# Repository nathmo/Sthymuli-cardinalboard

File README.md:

# Sthymuli-cardinalboard
companion boardto the sthymuli motherboard

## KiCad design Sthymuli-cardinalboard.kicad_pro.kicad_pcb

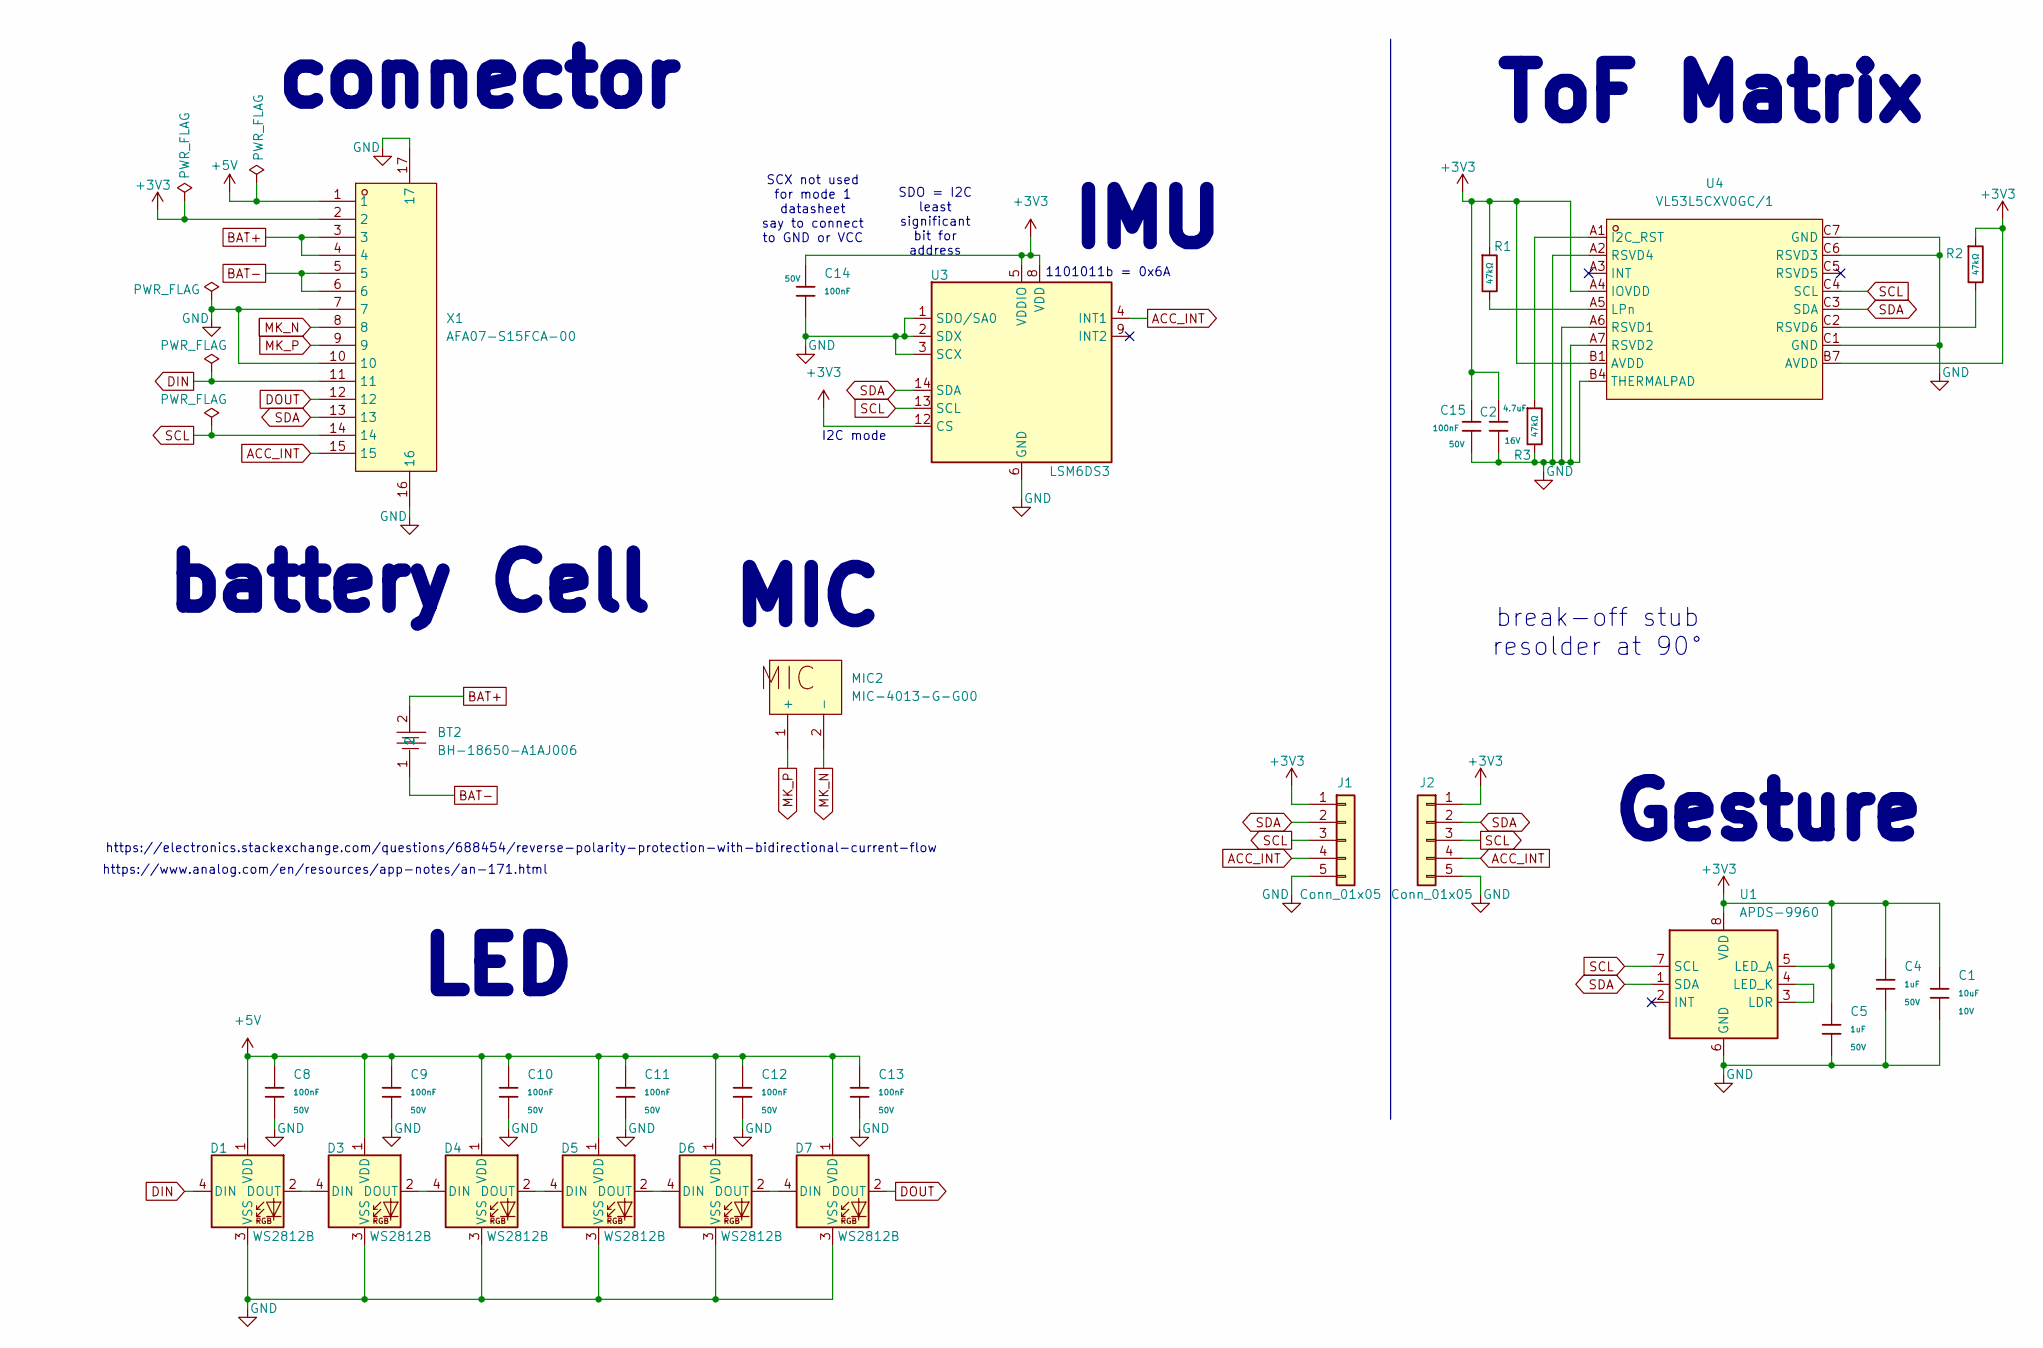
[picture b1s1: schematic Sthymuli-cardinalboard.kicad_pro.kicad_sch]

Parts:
BT2: BH-18650-A1AJ006; BAT-TH_BH-18650-A1AJ006; MPN BH-18650-A1AJ006; LCSC Part C5290175
C1: 10uF; C_0603; Voltage Rated 10V; Tolerance ±10%; Part CL10A106KP8NNNC; LCSC C19702
C2: 4.7uF; C_0603; Voltage Rated 16V; Tolerance ±10%; Part CL10A475KO8NNNC; LCSC C19666
C4, C5: 1uF; C_0603; Voltage Rated 50V; Tolerance ±10%; Part CL10A105KB8NNNC; LCSC C15849
C8, C9, C10, C11, C12, C13, C14, C15: 100nF; C_0603; Voltage Rated 50V; Tolerance ±10%; Part CC0603KRX7R9BB104; LCSC C14663
D1, D3, D4, D5, D6, D7: WS2812B; LED_WS2812B_PLCC4_5.0x5.0mm_P3.2mm
J1: Conn_01x05; PinHeader_1x05_P2.54mm_Vertical_SMD_Pin1Left
J2: Conn_01x05; PinHeader_1x05_P2.54mm_Horizontal
MIC2: MIC-4013-G-G00; MIC-SMD_BD4.0-4013_SMDA; MPN MIC-4013-G-G00; LCSC Part C42371093
R1, R2, R3: 47kΩ; R_0603; Overload Voltage (Max) 75V; Tolerance ±1%; Part 0603WAF4702T5E; LCSC C25819
U1: APDS-9960; Avago_APDS-9960
U3: LSM6DS3; LGA-14_3x2.5mm_P0.5mm_LayoutBorder3x4y
U4: VL53L5CXV0GC/1; LGA-16_L6.4-W3.0_VL53L5CXV0GC-1; MPN VL53L5CXV0GC/1; LCSC Part C3178303
X1: AFA07-S15FCA-00; FPC-SMD_15P-P1.00_JS_AFA07-S15XXX; MPN AFA07-S15FCA-00; LCSC Part C262721

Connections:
+3V3: C1.1, C2.1, C4.1, C5.1, C14.1, C15.1, J1.1, J2.1, R1.1, R2.1, U1.5 (LED_A), U1.8 (VDD), U3.5 (VDDIO), U3.8 (VDD), U3.12 (CS), U4.A4 (IOVDD), U4.B1 (AVDD), U4.B7 (AVDD), X1.2
+5V: C8.1, C9.1, C10.1, C11.1, C12.1, C13.1, D1.1 (VDD), D3.1 (VDD), D4.1 (VDD), D5.1 (VDD), D6.1 (VDD), D7.1 (VDD), X1.1
ACC_INT: J1.4, J2.4, U3.4 (INT1), X1.15
BAT+: BT2.2, X1.3, X1.4
BAT-: BT2.1, X1.5, X1.6
DIN: D1.4 (DIN), X1.11
DOUT: D7.2 (DOUT), X1.12
GND: C1.2, C2.2, C4.2, C5.2, C8.2, C9.2, C10.2, C11.2, C12.2, C13.2, C14.2, C15.2, D1.3 (VSS), D3.3 (VSS), D4.3 (VSS), D5.3 (VSS), D6.3 (VSS), D7.3 (VSS), J1.5, J2.5, R3.2, U1.6 (GND), U3.1 (SDO/SA0), U3.2 (SDX), U3.3 (SCX), U3.6 (GND), U3.7 (GND), U4.A2 (RSVD4), U4.A6 (RSVD1), U4.A7 (RSVD2), U4.B4 (THERMALPAD), U4.C1 (GND), U4.C6 (RSVD3), U4.C7 (GND), X1.7, X1.10, X1.16, X1.17
MK_N: MIC2.2 (-), X1.8
MK_P: MIC2.1 (+), X1.9
unnamed: D1.2 (DOUT), D3.4 (DIN)
unnamed: D3.2 (DOUT), D4.4 (DIN)
unnamed: D4.2 (DOUT), D5.4 (DIN)
unnamed: D5.2 (DOUT), D6.4 (DIN)
unnamed: D6.2 (DOUT), D7.4 (DIN)
unnamed: U1.3 (LDR), U1.4 (LED_K)
unnamed: R3.1, U4.A1 (I2C_RST)
unnamed: R1.2, U4.A5 (LPn)
unnamed: R2.2, U4.C2 (RSVD6)
SCL: J1.3, J2.3, U1.7 (SCL), U3.13 (SCL), U4.C4 (SCL), X1.14
SDA: J1.2, J2.2, U1.1 (SDA), U3.14 (SDA), U4.C3 (SDA), X1.13

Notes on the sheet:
https://www.analog.com/en/resources/app-notes/an-171.html
https://electronics.stackexchange.com/questions/688454/reverse-polarity-protection-with-bidirectional-current-flow
SCX not used for mode 1 datasheet say to connect to GND or VCC
IMU
1101011b = 0x6A
SDO = I2C least significant bit for address
I2C mode
battery Cell
ToF Matrix
MIC
Gesture
connector
LED
break-off stub resolder at 90°

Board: 2 copper layers, 29 parts (5 on the bottom side), 21 nets, no tracks yet.

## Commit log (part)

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2026-03-29 making cardinalboard project
2026-03-29 routing small board
2026-03-30 done routing
2026-03-31 tried autoroute...
2026-04-04 added autocompile action + STEP
2026-04-04 Auto-export KiCad PDFs
2026-04-04 regenerated output
2026-04-04 added file for production
2026-04-04 Add initial README.md for Cardinalboard project
2026-04-09 fixed resistor footprint, enabled all DRC, improved readability
2026-04-09 found a cheaper ws2812
2026-04-10 regenerated zip with fabrication file and removed obselete file
2026-04-10 removed one corrupted CSV
2026-04-10 fixed the POS file header (again)
2026-04-10 added BOM for double side placement
2026-04-10 forgot the ITR in the BOM...
2026-04-17 added step
